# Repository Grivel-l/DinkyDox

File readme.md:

DinkyDox
===

These are the KiCad PCB source files for the DinkyDox keyboard and the stl file for the case. A MiniDox's fork created by [LeReverandNox](https://github.com/lereverandnox) and myself.

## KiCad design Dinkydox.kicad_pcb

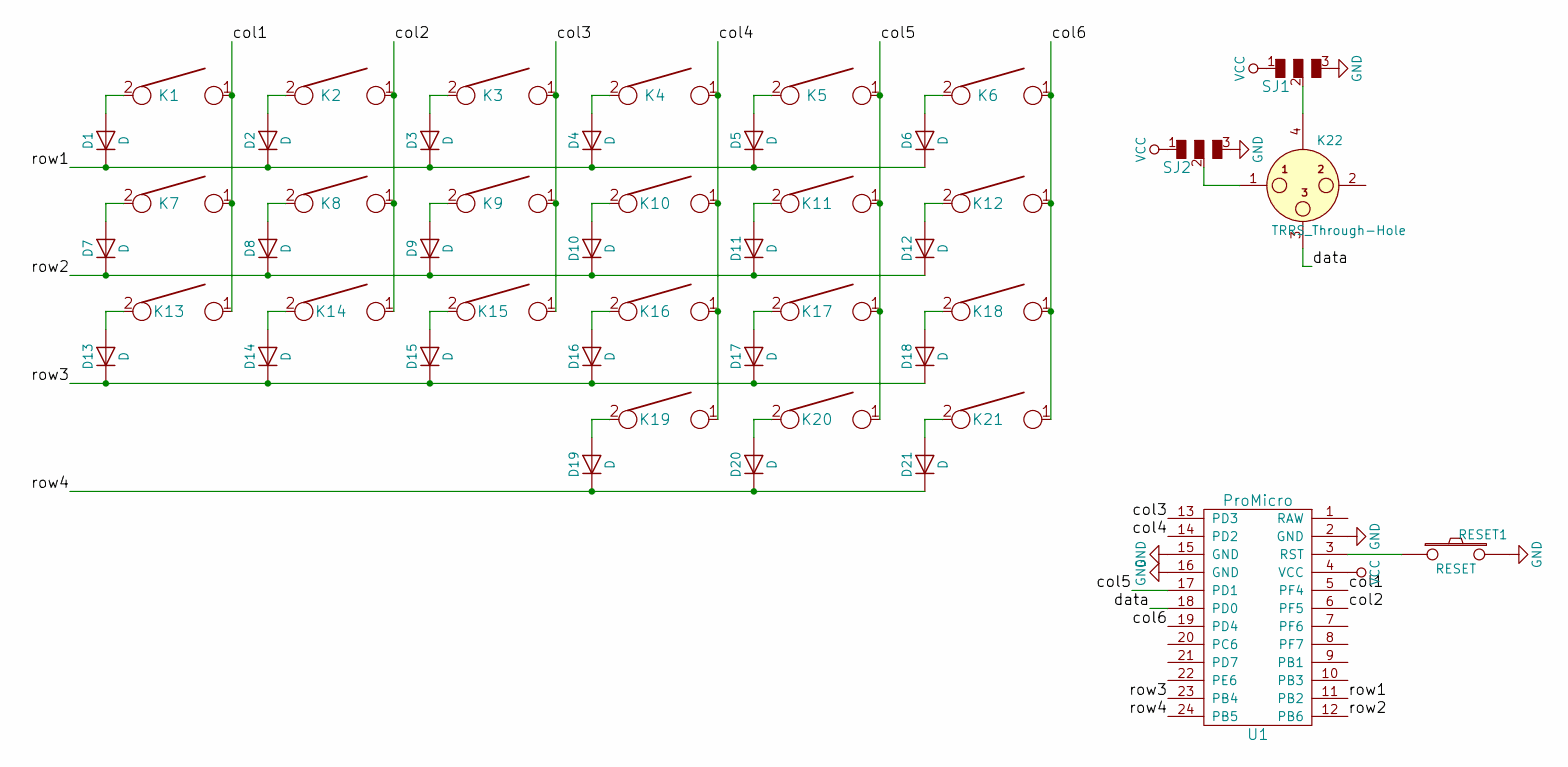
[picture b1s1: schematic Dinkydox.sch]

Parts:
D1, D2, D3, D4, D5, D6, D7, D8, D9, D10, D11, D12, D13, D14, D15, D16, D17, D18, D19, D20, D21: D; D_SOD123_axial-dual
K1, K2, K3, K4, K5, K6, K7, K8, K9, K10, K11, K12, K13, K14, K15, K16, K17, K18, K19, K20: KEYSW; Mx_Alps_100-dualside
K21: KEYSW; Mx_Alps_175-dualside
K22: TRRS_Through-Hole; 4pin35mmAudio-dualsided
RESET1: RESET; SW_SPST_TL3342
SJ1, SJ2: SOLDER_JUMPER_3
U1: ProMicro; Pro_Micro

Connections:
/col1: K1.1, K7.1, K13.1, U1.5 (PF4)
/col2: K2.1, K8.1, K14.1, U1.6 (PF5)
/col3: K3.1, K9.1, K15.1, U1.13 (PD3)
/col4: K4.1, K10.1, K16.1, K19.1, U1.14 (PD2)
/col5: K5.1, K11.1, K17.1, K20.1, U1.17 (PD1)
/col6: K6.1, K12.1, K18.1, K21.1, U1.19 (PD4)
/data: K22.3, U1.18 (PD0)
/row1: D1.1 (K), D2.1 (K), D3.1 (K), D4.1 (K), D5.1 (K), D6.1 (K), U1.11 (PB2)
/row2: D7.1 (K), D8.1 (K), D9.1 (K), D10.1 (K), D11.1 (K), D12.1 (K), U1.12 (PB6)
/row3: D13.1 (K), D14.1 (K), D15.1 (K), D16.1 (K), D17.1 (K), D18.1 (K), U1.23 (PB4)
/row4: D19.1 (K), D20.1 (K), D21.1 (K), U1.24 (PB5)
GND: RESET1.2, SJ1.3, SJ2.3, U1.2 (GND), U1.15 (GND), U1.16 (GND); also elsewhere on the board
unnamed: D1.2 (A), K1.2
unnamed: D2.2 (A), K2.2
unnamed: D3.2 (A), K3.2
unnamed: D4.2 (A), K4.2
unnamed: D5.2 (A), K5.2
unnamed: D6.2 (A), K6.2
unnamed: D7.2 (A), K7.2
unnamed: D8.2 (A), K8.2
unnamed: D9.2 (A), K9.2
unnamed: D10.2 (A), K10.2
unnamed: D11.2 (A), K11.2
unnamed: D12.2 (A), K12.2
unnamed: D13.2 (A), K13.2
unnamed: D14.2 (A), K14.2
unnamed: D15.2 (A), K15.2
unnamed: D16.2 (A), K16.2
unnamed: D17.2 (A), K17.2
unnamed: D18.2 (A), K18.2
unnamed: D19.2 (A), K19.2
unnamed: D20.2 (A), K20.2
unnamed: D21.2 (A), K21.2
unnamed: K22.1, SJ2.2
unnamed: K22.4, SJ1.2
unnamed 36: RESET1.1, U1.3 (RST); also elsewhere on the board
VCC: SJ1.1, SJ2.1, U1.4 (VCC)

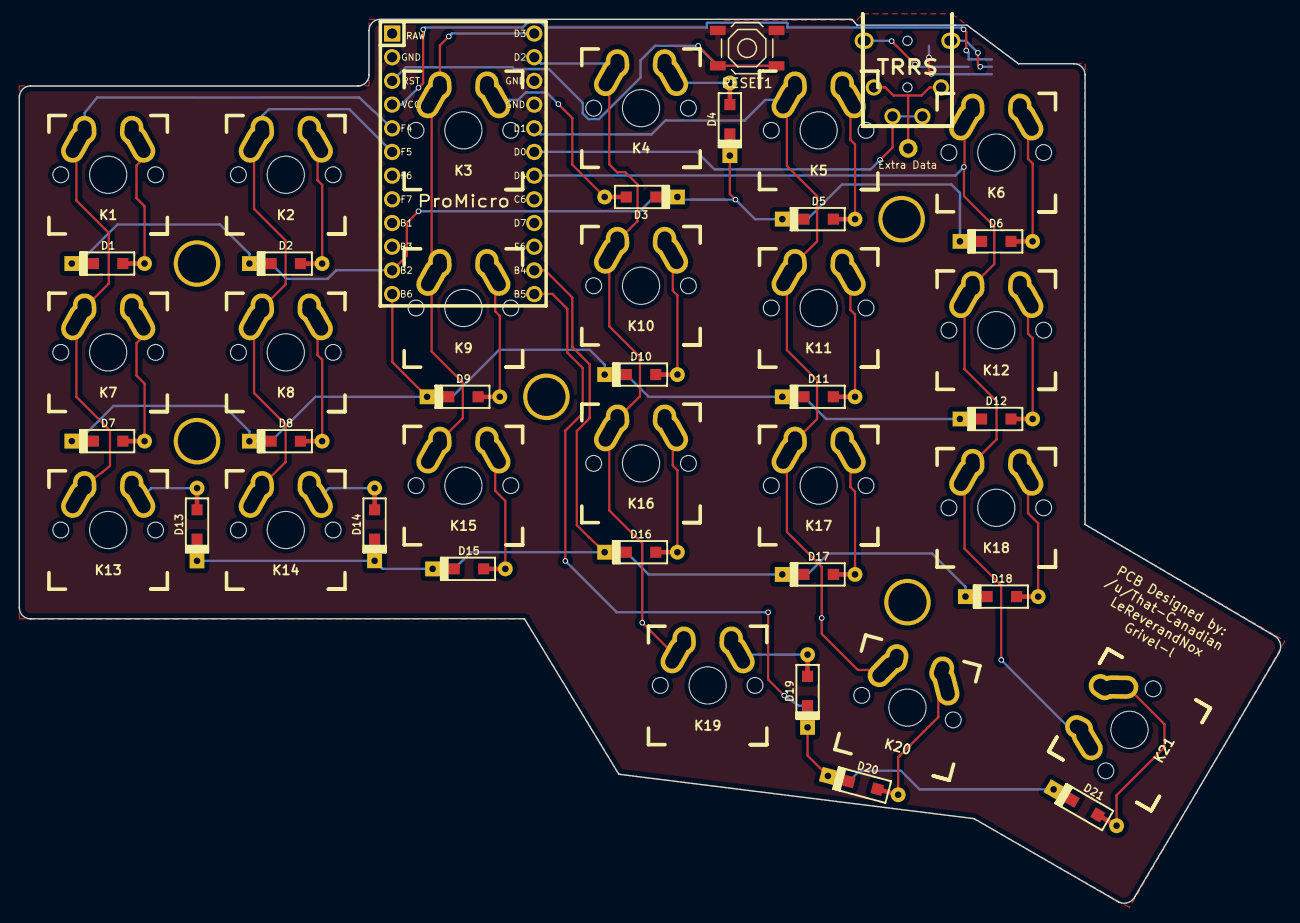
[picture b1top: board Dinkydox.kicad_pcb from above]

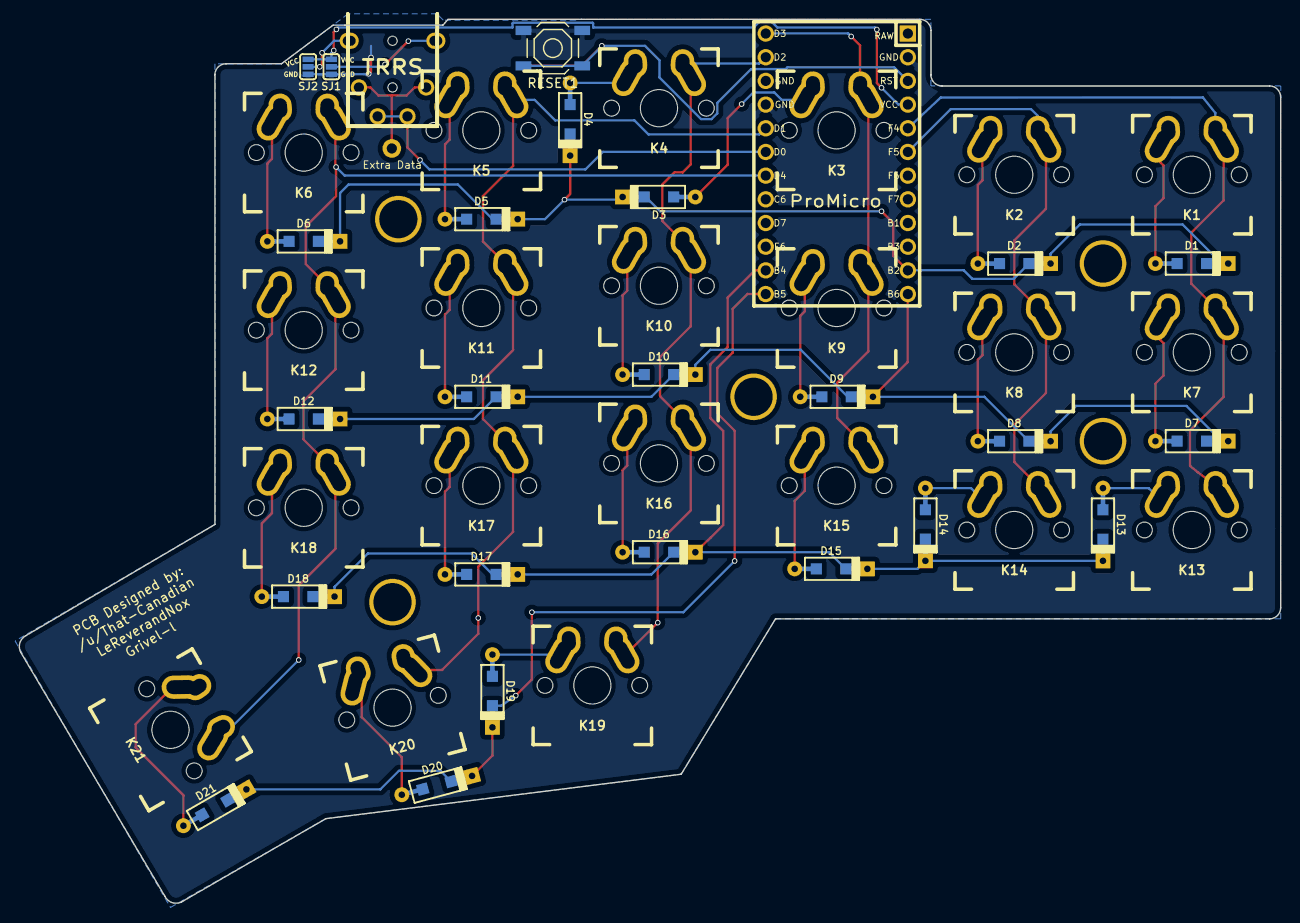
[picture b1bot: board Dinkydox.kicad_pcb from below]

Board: 2 copper layers, 135.3 x 94.8 mm, 48 parts (24 on the bottom side), 37 nets.

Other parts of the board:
RESET1#2: RESET; SW_SPST_TL3342

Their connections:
GND: RESET1#2.2; also elsewhere on the board
unnamed 36: RESET1#2.1; also elsewhere on the board

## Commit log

2020-04-16 Rename 6col
2020-04-16 Update readme with DinkyDox's infos
2020-11-26 Add 3d file for the case
2020-11-26 Add case to the readme
2020-11-26 Reversed some normals
2020-12-04 Add standoffs and wrist rest
